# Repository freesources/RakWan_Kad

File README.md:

# RakWan_Kad
Small lorawan pager
Kicad Files

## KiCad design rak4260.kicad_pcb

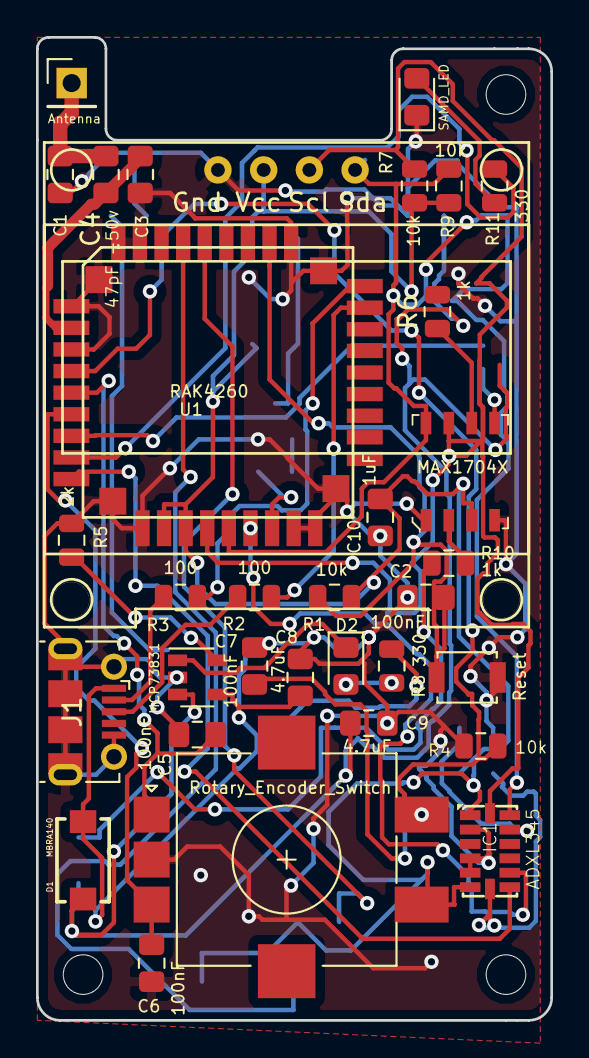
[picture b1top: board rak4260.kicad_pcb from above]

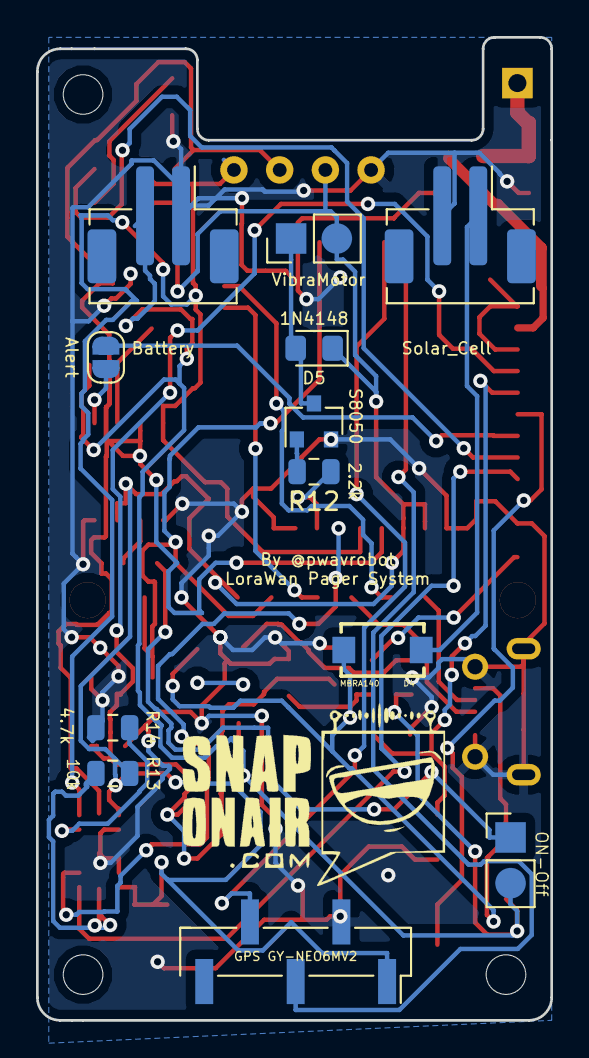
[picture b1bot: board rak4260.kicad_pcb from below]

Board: 2 copper layers, 28.6 x 54.6 mm, 48 parts (12 on the bottom side), 36 nets.

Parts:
AE1: Antenna; PinHeader_1x01_P2.54mm_Vertical
C1, C4: NC; C_0805_2012Metric_Pad1.15x1.40mm_HandSolder
C2, C5, C6, C7: 100nF; C_0805_2012Metric_Pad1.15x1.40mm_HandSolder
C3: 47pF -50v; C_0805_2012Metric_Pad1.15x1.40mm_HandSolder
C8, C9: 4.7uF; C_0805_2012Metric_Pad1.15x1.40mm_HandSolder
C10: 1uF; C_0805_2012Metric_Pad1.15x1.40mm_HandSolder
D1, D4: MBRA140
D2: CHRG_LED; LED_0805_2012Metric_Pad1.15x1.40mm_HandSolder
D3: SAMD_LED; LED_0805_2012Metric_Pad1.15x1.40mm_HandSolder
D5: 1N4148; D_0805_2012Metric_Pad1.15x1.40mm_HandSolder
H1, H2, H3: MountingHole; MountingHole_2.2mm_M2
IC1: ADXL345
J1: USB_OTG; USB_Micro-B_Molex-105017-0001
J2: Battery; JST_PH_B2B-PH-SM4-TB_1x02-1MP_P2.00mm_Vertical
J3: GPS GY-NEO6MV2; PinHeader_1x05_P2.54mm_Vertical_SMD_Pin1Right
J4: VibraMotor; VibraPads
JP1: Alert; SolderJumper-2_P1.3mm_Open_RoundedPad1.0x1.5mm
LCD1: Oled96
Q1: S8050; SOT-23
R1, R4, R7, R9, R13: 10k; R_0805_2012Metric
R2, R3: 100; R_0805_2012Metric
R5: 2k; R_0805_2012Metric
R6, R10: 1k; R_0805_2012Metric
R8, R11: 330; R_0805_2012Metric
R12: 2.2k; R_0805_2012Metric
R14: 4.7k; R_0805_2012Metric
SC1: Solar_Cell; JST_PH_B2B-PH-SM4-TB_1x02-1MP_P2.00mm_Vertical
SW1: Reset; SW_SPST_B3U-1000P
SW2: Rotary_Encoder_Switch; RotaryEncoder_Alps_EC11E-Switch_Vertical_H20mm
SW3: ON-Off; VibraPads
U1: RAK4260
U2: MCP73831; SOT-23-5
U3: MAX1704X; TDFN-8-1EP

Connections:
+3V3: C10.2, D5.1, IC1.1, IC1.6, J3.1, J4.2, LCD1.3, R1.2, R7.1, R9.1, R13.2, SW2.S1, U1.11, U1.12, U3.3
/AlertB: JP1.2, U1.7
/INT1: IC1.8, U1.9
/INT2: IC1.9, U1.15
/PinMotor: R12.1, U1.16
/RE+: C5.1, SW2.A, U1.5
/RE-: C6.1, SW2.B, U1.6
/RFC: C3.2, C4.2, U1.2
/RPressed: C7.1, R4.1, SW2.S2, U1.4
/RST: C2.2, R1.1, SW1.1, U1.29
/RXD: J3.4, U1.32
/SAMLED: R11.2, U1.8
/SCL: IC1.14, LCD1.2, R7.2, U1.13, U3.7
/SDA: IC1.13, LCD1.1, R9.2, U1.14, U3.8
/TXD: J3.3, U1.33
/USB_N: R3.1, U1.27
/USB_P: R2.1, U1.26
GND: C1.2, C2.1, C4.1, C5.2, C6.2, C7.2, C8.2, C9.2, C10.1, D3.1, IC1.2, IC1.4, IC1.5, J1.5, J1.6, J2.1, J3.2, LCD1.4, Q1.2, R4.2, R5.2, R6.2, R14.2, SC1.2, SW1.2, SW2.C, U1.1, U1.3, U1.10, U1.17, U1.18, U1.28, U1.35, U1.36, U1.37, U2.2, U3.1, U3.4
unnamed: AE1.1, C1.1, C3.1
unnamed: D2.1, U2.1
unnamed: D2.2, R8.1
unnamed: D3.2, R11.1
unnamed: D5.2, J4.1, Q1.3
unnamed: IC1.7, R13.1
unnamed: IC1.12, R14.1
unnamed: J1.2, R3.2
unnamed: J1.3, R2.2
unnamed: JP1.1, U3.5
unnamed: Q1.1, R12.2
unnamed: R5.1, U2.5
unnamed: R6.1, U3.6
unnamed: R10.1, SW3.1
unnamed: R10.2, U3.2
VBAT: C9.1, D1.A, J2.2, SW3.2, U2.3
V_BUS: C8.1, D1.C, D4.C, J1.1, R8.2, U2.4
V_Solar: D4.A, SC1.1

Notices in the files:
rak4260.kicad_pcb:
Public Domain work
